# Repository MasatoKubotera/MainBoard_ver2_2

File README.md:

<html lang="en">
  <head>
    <meta charset="uft-8">
    <meta name="author" content="Masato Kubotera">
  </head>
  <body>
    <h1>Main Board Ver. 2.2</h1>
    <h2>About Main Board</h2>
    <p>
      The Main Board is a single board that integrates the circuits for driving the robot designed to be mounted on SUSTAINA-OP.
      <br>
      <br>
      Note that this is Ver. 2.2. For other versions, please refer to the following repositories.
      <ul>
        <li><a href="https://github.com/MasatoKubotera/MainBoard_ver2_0">Main Board Ver. 2.0</a></li>
        <li><a href="https://github.com/MasatoKubotera/MainBoard_ver2_1">Main Board Ver. 2.1</a></li>
      </ul>
      <h2>About Ver. 2.2</h2>
      now writing...
      <br><br>
      It is actually used for the 6th generation robot SUSTAINA-OP of the RoboCup Humanoid League team CIT Brains competed in the RoboCup 2022.<br><br>
      <!--
      -->
      <table>
        <tr>
          <td>
            <a href="image/brd_top.png">
              <div align="center">
                
              </div>
            </a>
          </td>
          <td>
            <div align="center">
              
            </div>
          </td>
          <td>
            <div align="center">
              
            </div>
          </td>
        </tr>
        <tr>
          <td>
            <div align="center">
              PCB preview image
            </div>
          </td>
          <td>
            <div align="center">
              After mounting electronic components
            </div>
          </td>
          <td>
            <div align="center">
              After attaching module board
            </div>
          </td>     
        </tr>
      </table>
    </p>
    <h2>Repository Contents</h2>
    <p>
    <dl>
      <dt>\image</dt>
      <dd>PCB preview images and capture of design screen</dd>
      <dt>\libraries</dt>
      <dd>Libraries used in Autodesk Eagle design</dd>
      <dt>Schematic.pdf</dt>
      <dd>Circuit diagram of this product</dd>
      <dt>BOM.txt</dt>
      <dd>Parts lists output from design data</dd>
      <dt>.brd</dt>
      <dd>Board wiring design file by Autodesk Eagle</dd>
      <dt>.sch</dt>
      <dd>Schematic design file by Autodesk Eagle</dd>
      <dt>Gerber_data.zip</dt>
      <dd>Zip folder of Gerber format files for PCB manufacturing requests.</dd>
      <dt>LICENSE</dt>
      <dd>This is a license to use this product. Please confirm before use.</dd>
      <dt>.gitignore</dt>
      <dd>File to exclude cache files from management.</dd>
    </dl>
    </p>
    <h2>Documentation</h2>
      <p>
        <h3>BOM</h3>
        The BOM below shows the components actually mounted on the SUSTAINA-OP equipped MainBoard in RoboCup2022. Many of these boards have been created, and in some cases substitutes have been used. Their details are listed below the BOM.
          <table>
            <thead>
              <tr>
                <th> Eagle Design Parts # </th>
                <th> Q'ty </th>
                <th> Mfr. Product # </th>
                <th> Supplier </th>
                <th> Description </th>
              </tr>
            </thead>
            <tbody>
              <tr>
                <td>C1, C2, C3, C4, C5, C6</td>
                <td>6</td>
                <td>C1608JB1H104K</td>
                <td><a href="https://akizukidenshi.com/catalog/g/gP-06166/">Akizuki</a></td>
                <td>Multilayer Ceramic Capacitors SMD/SMT 0.1uF 50V 10% 0603</td>
              </tr>
              <tr>
                <td>C11,C15</td>
                <td>2</td>
                <td>UWT1E221MNL1GS</td>
                <td><a href="https://akizukidenshi.com/catalog/g/gP-10420/">Akizuki</a></td>
                <td>Aluminum Electrolytic Capacitors SMD/SMT 220uF 25V 20% AEC-Q200</td>
              </tr>
              <tr>
                <td>C12,C14</td>
                <td>2</td>
                <td>GRM188R71E105KA12</td>
                <td><a href="https://akizukidenshi.com/catalog/g/gP-14526/">Akizuki</a></td>
                <td>Multilayer Ceramic Capacitors SMD/SMT 1uF 25V 10% 0603</td>
              </tr>
              <tr>
                <td>C13</td>
                <td>1</td>
                <td>GRM21BR61E226ME44</td>
                <td><a href="https://akizukidenshi.com/catalog/g/gP-08240/">Akizuki</a></td>
                <td>Multilayer Ceramic Capacitors SMD/SMT 22uF 25V 15% 0603</td>
              </tr>
              <tr>
                <td>C16</td>
                <td>1</td>
                <td>GRM188R6YA106MA73</td>
                <td><a href="https://akizukidenshi.com/catalog/g/gP-13161/">Akizuki</a></td>
                <td>Multilayer Ceramic Capacitors SMD/SMT 10uF 35V 20% 0603</td>
              </tr>
              <tr>
                <td>C7, C8, C9, C10</td>
                <td>4</td>
                <td>35PFV150M8X10.5</td>
                <td><a href="https://akizukidenshi.com/catalog/g/gP-14492/">Akizuki</a></td>
                <td>Aluminum Organic Polymer Capacitors SMD/SMT 150uF 35V 20% AEC-Q200</td>
              </tr>
              <tr>
                <td>CH1, CH2</td>
                <td>2</td>
                <td>XT60PW-M</td>
                <td><a href="https://store.shopping.yahoo.co.jp/suzakulab/amass-xt60pw-m.html">Suzaku Lab.</a></td>
                <td>DC Power Connector, Through Hole, Horizontal, Male, 30A 500V</td>
              </tr>
              <tr>
                <td>CH3</td>
                <td>1</td>
                <td>B2B-XH-A-BLACK</td>
                <td><a href="https://www.daisen-netstore.com/shopdetail/000000000029/ct15/page1/order/">DAISEN</a></td>
                <td>Connector Header Through Hole, Top entry 2 position 2.54mm BLACK</td>
              </tr>
              <tr>
                <td>CH4</td>
                <td>1</td>
                <td>B2B-XH-A-BLUE</td>
                <td><a href="https://www.daisen-netstore.com/shopdetail/000000000029/ct15/page1/order/">DAISEN</a></td>
                <td>Connector Header Through Hole, Top entry 2 position 2.54mm BLUE</td>
              </tr>
              <tr>
                <td>CH5</td>
                <td>1</td>
                <td>B2B-XH-A-GREEN</td>
                <td><a href="https://www.daisen-netstore.com/shopdetail/000000000029/ct15/page1/order/">DAISEN</a></td>
                <td>Connector Header Through Hole, Top entry 2 position 2.54mm GREEN</td>
              </tr>
              <tr>
                <td>CH6</td>
                <td>1</td>
                <td>B2B-XH-A-YELLOW</td>
                <td><a href="https://www.daisen-netstore.com/shopdetail/000000000029/ct15/page1/order/">DAISEN</a></td>
                <td>Connector Header Through Hole, Top entry 2 position 2.54mm YELLOW</td>
              </tr>
              <tr>
                <td>CH7</td>
                <td>1</td>
                <td>B2B-XH-A-RED</td>
                <td><a href="https://www.daisen-netstore.com/shopdetail/000000000029/ct15/page1/order/">DAISEN</a></td>
                <td>Connector Header Through Hole, Top entry 2 position 2.54mm RED</td>
              </tr>
              <tr>
                <td>CH8, CH9</td>
                <td>2</td>
                <td>S4B-XH-A(LF)(SN)-YELLOW</td>
                <td><a href="https://www.daisen-netstore.com/shopdetail/000000000028/ct15/page1/order/">DAISEN</a></td>
                <td>Connector Header Through Hole, Side entry 4 position 2.54mm YELLOW</td>
              </tr>
              <tr>
                <td>CH10</td>
                <td>1</td>
                <td>S4B-XH-A(LF)(SN)-GREEN</td>
                <td><a href="https://www.daisen-netstore.com/shopdetail/000000000028/ct15/page1/order/">DAISEN</a></td>
                <td>Connector Header Through Hole, Side entry 4 position 2.54mm GREEN</td>
              </tr>
              <tr>
                <td>CH11, CH12</td>
                <td>2</td>
                <td>S4B-XH-A(LF)(SN)-BLUE</td>
                <td><a href="https://www.daisen-netstore.com/shopdetail/000000000028/ct15/page1/order/">DAISEN</a></td>
                <td>Connector Header Through Hole, Side entry 4 position 2.54mm BLUE</td>
              </tr>
              <tr>
                <td>CH13</td>
                <td>1</td>
                <td>S4B-XH-A(LF)(SN)-RED</td>
                <td><a href="https://www.daisen-netstore.com/shopdetail/000000000028/ct15/page1/order/">DAISEN</a></td>
                <td>Connector Header Through Hole, Side entry 4 position 2.54mm RED</td>
              </tr>
              <tr>
                <td>D1</td>
                <td>1</td>
                <td>SS34FA</td>
                <td><a href="https://www.mouser.jp/ProductDetail/512-SS34FA">Mouser</a></a></td>
                <td>Schottky Barrier Rectifiers SMD/SMT 3 A 40 V</td>
              </tr>
              <tr>
                <td>F1, F2, F4</td>
                <td>3</td>
                <td>0891020.NXS</td>
                <td><a href="https://www.mouser.jp/ProductDetail/576-0891020.NXS">Mouser</a></td>
                <td>Automotive Fuses LP MINI 58V 20A</td>
              </tr>
              <tr>
                <td>F1, F2, F4, F6</td>
                <td>4</td>
                <td>3557-2</td>
                <td><a href="https://www.mouser.jp/ProductDetail/534-3557-2">Mouser</a></td>
                <td>Fuse Holder Through Hole 500V 30A</td>
              </tr>
              <tr>
                <td>F3</td>
                <td>1</td>
                <td>MF-MSMF010</td>
                <td><a href="https://akizukidenshi.com/catalog/g/gP-15428/">Akizuki</a></td>
                <td>PTC Resettable Fuses SMD/SMT 0.1A 60V 1812</td>
              </tr>
              <tr>
                <td>F5</td>
                <td>1</td>
                <td>MF-MSMF050/30X-2</td>
                <td><a href="https://www.mouser.jp/ProductDetail/652-MF-MSMF050/30X-2">Mouser</a></td>
                <td>PTC Resettable Fuses SMD/SMT 0.5A 30V 1812</td>
              </tr>
              <tr>
                <td>F6</td>
                <td>1</td>
                <td>MO-29</td>
                <td><a href="https://www.amazon.co.jp/dp/B0722VT9DQ/">Amazon</a></td>
                <td>Automotive Fuses LP MINI 7.5A</td>
              </tr>
              <tr>
                <td>IC1, IC2, IC3, IC4</td>
                <td>4</td>
                <td>ADM3078EARZ</td>
                <td><a href="https://www.mouser.jp/ProductDetail/584-ADM3078EARZ">Mouser</a></td>
                <td>3.3 V, ±15 kV ESD-Protected, Half- and Full-Duplex, RS-485/RS-422 Transceivers</td>
              </tr>
              <tr>
                <td>IC5</td>
                <td>1</td>
                <td>LTC4412ES6</td>
                <td><a href="https://akizukidenshi.com/catalog/g/gI-07305/">Akizuki</a></td>
                <td>PMIC Low Loss PowerPath Controller</td>
              </tr>
              <tr>
                <td>L1,L2</td>
                <td>2</td>
                <td>CDRH127/LDNP-470MC</td>
                <td><a href="https://akizukidenshi.com/catalog/g/gP-13966/">Akizuki</a></td>
                <td>Power Inductors - SMD 47uH 3.25A</td>
              </tr>
              <tr>
                <td>L3</td>
                <td>1</td>
                <td>DFE201210S-2R2M</td>
                <td><a href="https://akizukidenshi.com/catalog/g/gP-14976/">Akizuki</a></td>
                <td>Power Inductors - SMD 2.2 uH 1.5A</td>
              </tr>
              <tr>
                <td>LED1,LED2,LED3,LED4</td>
                <td>4</td>
                <td>150060VS86000</td>
                <td><a href="https://www.mouser.jp/ProductDetail/710-150060VS86000">Mouser</a></td>
                <td>Standard LEDs - SMD Green 2V 20mA 573nm 0603</td>
              </tr>
              <tr>
                <td>LED5,LED6</td>
                <td>2</td>
                <td>150060YS75000</td>
                <td><a href="https://www.mouser.jp/ProductDetail/710-150060YS75000">Mouser</a></td>
                <td>Standard LEDs - SMD Yellow 2V 20mA 590nm 0603</td>
              </tr>
              <tr>
                <td>M1</td>
                <td>1</td>
                <td>FT4232H MINI MODULE</td>
                <td><a href="https://www.mouser.jp/ProductDetail/895-FT4232HMINIMOD">Mouser</a></td>
                <td>Interface Development Tools USB Hi-Speed FT4323H Evaluation Module</td>
              </tr>
              <tr>
                <td>M1</td>
                <td>2</td>
                <td>FH-2x13SG</td>
                <td><a href="https://akizukidenshi.com/catalog/g/gC-00084/">Akizuki</a></td>
                <td>2.54mm Pin Socket, 2 Row, 26 Pin</td>
              </tr>
              <tr>
                <td>Q1, Q2, Q3, Q4, Q5</td>
                <td>5</td>
                <td>SQM40P10-40L_GE3</td>
                <td><a href="https://www.mouser.jp/ProductDetail/78-SQM40P10-40L_GE3">Mouser</a></td>
                <td>Pch MOSFET 100V 40A 150W 33mohm</td>
              </tr>
              <tr>
                <td>R1, R3, R4, R6, R7, R9, R10, R12</td>
                <td>8</td>
                <td>RC0603FR-10680RL</td>
                <td><a href="https://www.mouser.jp/ProductDetail/603-RC0603FR-10680RL">Mouser</a></td>
                <td>Thick Film Resistors - SMD 680 Ohms 100-200mW 1% 0603</td>
              </tr>
              <tr>
                <td>R13, R14, R22</td>
                <td>3</td>
                <td>RC0603FR-101KL</td>
                <td><a href="https://www.mouser.jp/ProductDetail/603-RC0603FR-101KL">Mouser</a></td>
                <td>Thick Film Resistors - SMD 1 kOhms 100-200mW 1% 0603</td>
              </tr>
              <tr>
                <td>R15, R16, R20, R23</td>
                <td>4</td>
                <td>RC0603FR-102KL</td>
                <td><a href="https://www.mouser.jp/ProductDetail/603-RC0603FR-102KL">Mouser</a></td>
                <td>Thick Film Resistors - SMD 2 kOhms 100-200mW 1% 0603</td>
              </tr>
              <tr>
                <td>R17</td>
                <td>1</td>
                <td>RC0603FR-10470KL</td>
                <td><a href="https://www.mouser.jp/ProductDetail/603-RC0603FR-10470KL">Mouser</a></td>
                <td>Thick Film Resistors - SMD 470 kOhms 100-200mW 1% 0603</td>
              </tr>
              <tr>
                <td>R21</td>
                <td>1</td>
                <td>RC0603FR-078K66L</td>
                <td><a href="https://www.mouser.jp/ProductDetail/603-RC0603FR-078K66L">Mouser</a></td>
                <td>Thick Film Resistors - SMD 8.66 kOhms 100-200mW 1% 0603</td>
              </tr>
              <tr>
                <td>R18, R19</td>
                <td>2</td>
                <td>RC0603FR-1010KL</td>
                <td><a href="https://www.mouser.jp/ProductDetail/603-RC0603FR-1010KL">Mouser</a></td>
                <td>Thick Film Resistors - SMD 10 kOhms 100-200mW 1% 0603</td>
              </tr>
              <tr>
                <td>R2, R5, R8, R11</td>
                <td>4</td>
                <td>RC0603FR-10120RL</td>
                <td><a href="https://www.mouser.jp/ProductDetail/603-RC0603FR-10120RL">Mouser</a></td>
                <td>Thick Film Resistors - SMD 120 Ohms 100-200mW 1% 0603</td>
              </tr>
              <tr>
                <td>VR1</td>
                <td>1</td>
                <td>XL6009E1</td>
                <td><a href="https://www.aitendo.com/product/10307">Aitendo</a></td>
                <td>400KHz 60V 4A Switching Current Boost / Buck-Boost / Inverting DC/DC Converter</td>
              </tr>
            </tbody>
          </table>
          <details>
            <summary>Substitutes</summary>
            Used for No. 1 ~ No. 7
            <table>
              <thead>
                <tr>
                  <th> Eagle Design Parts # </th>
                  <th> Q'ty </th>
                  <th> Mfr. Product # </th>
                  <th> Supplier </th>
                  <th> Description </th>
                </tr>
              </thead>
              <tbody>
                <tr>
                  <td>C1, C2, C3, C4, C5, C6</td>
                  <td>6</td>
                  <td>GCM188L81H104K57</td>
                  <td><a href="https://akizukidenshi.com/catalog/g/gP-16143/">Akizuki</a></td>
                  <td>Multilayer Ceramic Capacitors SMD/SMT 0.1uF 50V 10% 0603</td>
                </tr>
              </tbody>
            </table>
            Used for No. 13 ~ 
            <table>
              <thead>
                <tr>
                  <th> Eagle Design Parts # </th>
                  <th> Q'ty </th>
                  <th> Mfr. Product # </th>
                  <th> Supplier </th>
                  <th> Description </th>
                </tr>
              </thead>
              <tbody>
                <tr>
                  <td>Q1, Q2, Q3, Q4, Q5</td>
                  <td>5</td>
                  <td>SUM110P06-08L-E3</td>
                  <td><a href="https://www.mouser.jp/ProductDetail/781-SUM110P06-08L-E3">Mouser</a></td>
                  <td>Pch MOSFET 60V 110A 272W 8.0mohm</td>
                </tr>
              </tbody>
            </table>
          </details>  
        <h3>PCB Fabrication</h3>
          PCB(Printed Circuit Board) manufacturing was outsourced to <a href="https://www.elecrow.com/pcb-manufacturing.html">Elecrow</a>.<br>
          The custom specifications are as follows.
          <ul>
            <li>Layer : 2 layers</li>
            <li>Dimensions : 120 x 65</li>
            <li>Different PCB Design : 1eg</li>
            <li>PCB Thickness : 1.6</li>
            <li>PCB Color : Black</li>
            <li>Surface Finish : HASL Lead Free</li>
            <li>Castellated Hole : No</li>
            <li>Copper Weight : 2oz</li>
            <li>PCB Stencil : Stencil 15cm X 15cm no frame</li>
            <li>Stencil Side : Top</li>
          </ul>
          The data used to order fabrication are as follows.
          <ul>
            <li>Eagle design rule : <a href="https://www.elecrow.com/download/Elecrow_PCB_eagle_rule.zip">Elecrow Eagle Design Rule</a></li>
            <li>Eagle CAM file : <a href="https://www.elecrow.com/download/Elecrow_Gerber_Generater_DrillAlign.zip">Elecrow CAM file</a></li>
            <li>Gerber format data : <a href="/Gerber_data.zip">Gerber_data.zip</a></li>
          </ul>
        <h3>Issues with this board</h3>
        <ul>
          <li>Heat generation problem of FETs</li>
          <li>Poor inrush current protection by load switch circuit</li>
        </ul>
        <h3>References</h3>
        <ul>
          <li> 4-Parallel Servo Motor Control with FT4232H MINI MODULE
            <ul>
              <li> <a href=""https://2019.robocup.org/downloads/program/BestmannEtAl2019.pdf">Bestmann, Marc & Güldenstein, Jasper & Zhang, Jianwei. (2019). High-Frequency Multi Bus Servo and Sensor Communication Using the Dynamixel Protocol. </a></li>
              <li> Wolfgang CORE : https://github.com/bit-bots/wolfgang_core</li>
             </ul>
          </li>
        </ul>
      </p>
    <h2>Contact</h2>
    <p>
    If you have any questions, please contact MasatoKubotera, the product's designer, by E-mail.<br>
    E-mail : <a href="mailto:masatokubotera06@yahoo.co.jp">masatokubotera06@yahoo.co.jp</a>
    </p>
    <h2>License Information</h2>
    <p>
      This product is open source.<br>
      Please review the <a href="/LICENSE">LICENSE file</a> for license information.<br>
      <br>
      <strong>Main Board Ver. 2.2</strong> by Masato Kubotera is licensed under a <a href="http://creativecommons.org/licenses/by-nc-sa/4.0/">Creative Commons Attribution-NonCommercial-ShareAlike 4.0 International License</a>.
    </p>    
  </body>
</html>

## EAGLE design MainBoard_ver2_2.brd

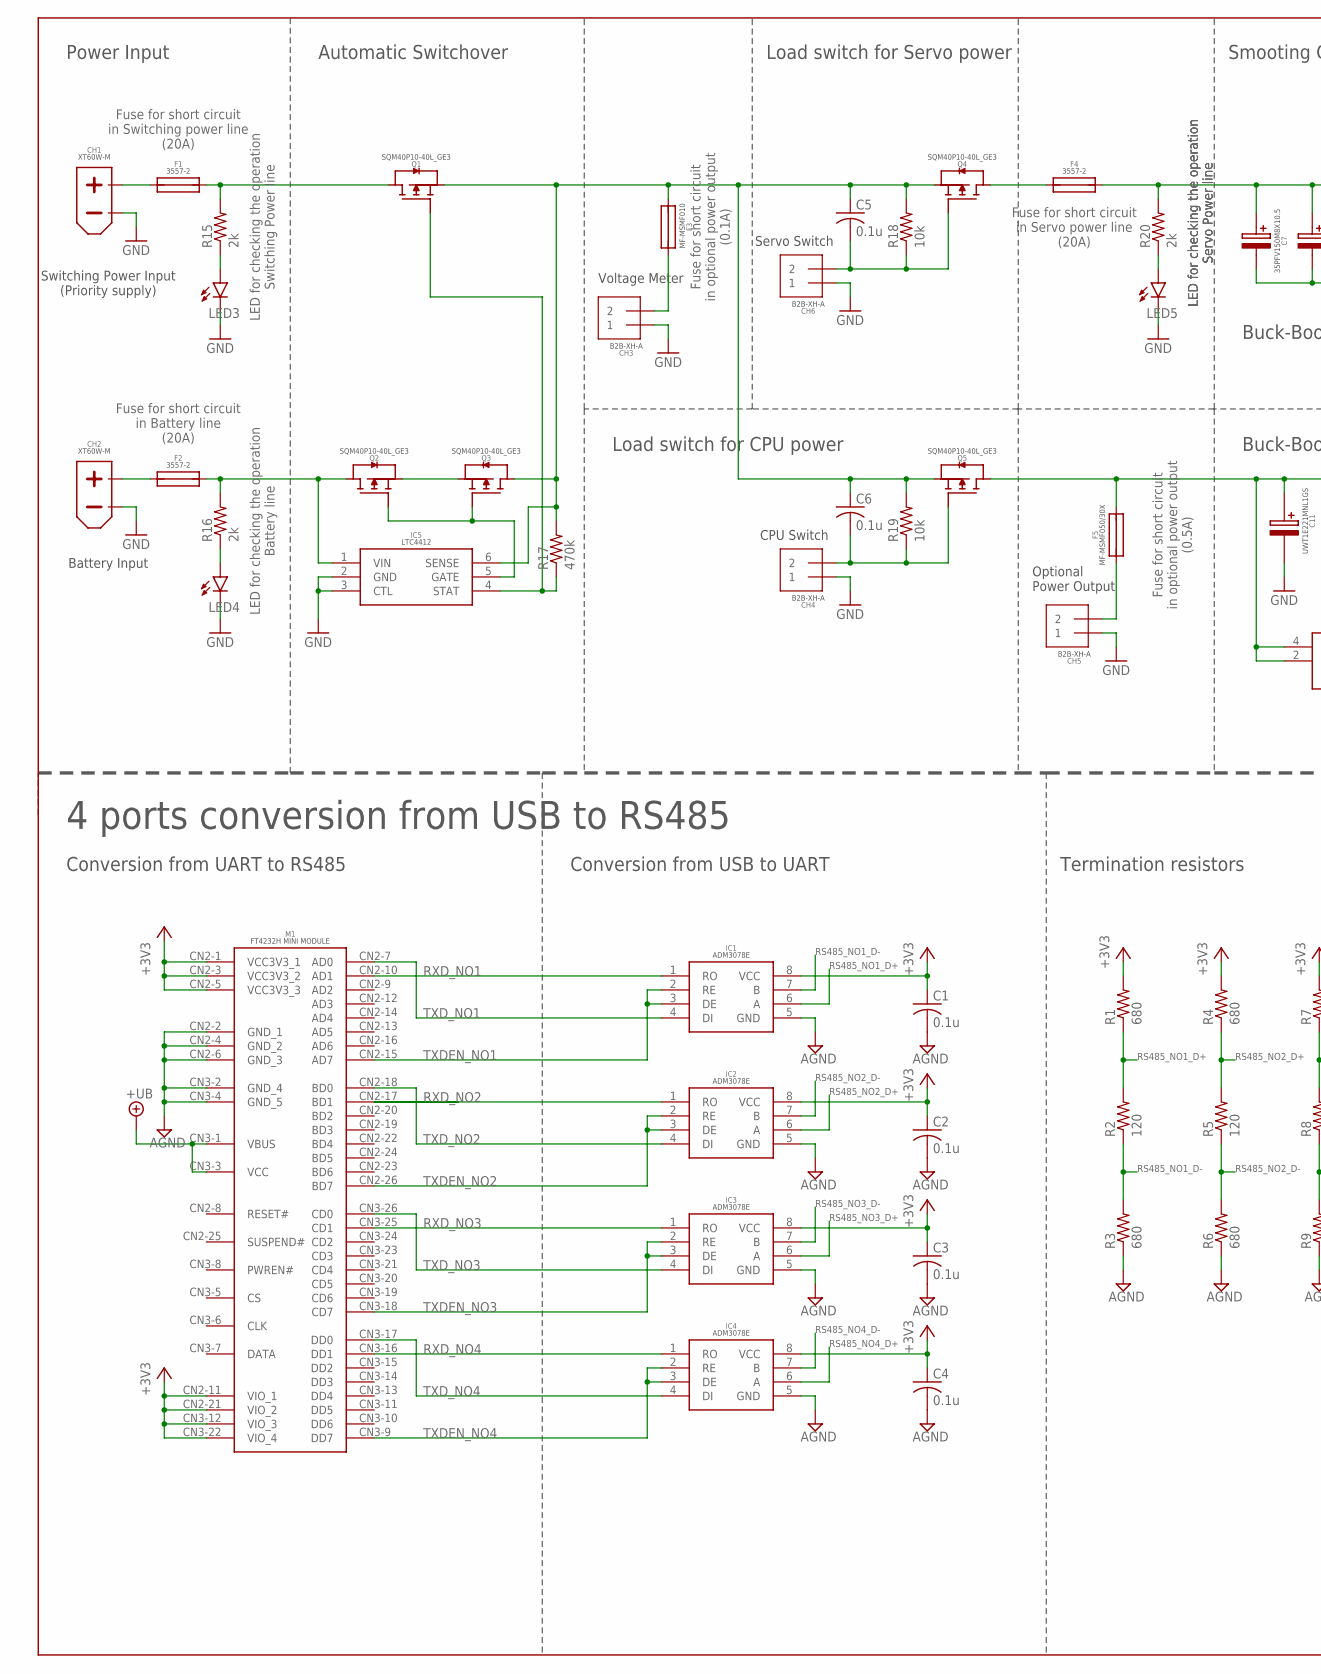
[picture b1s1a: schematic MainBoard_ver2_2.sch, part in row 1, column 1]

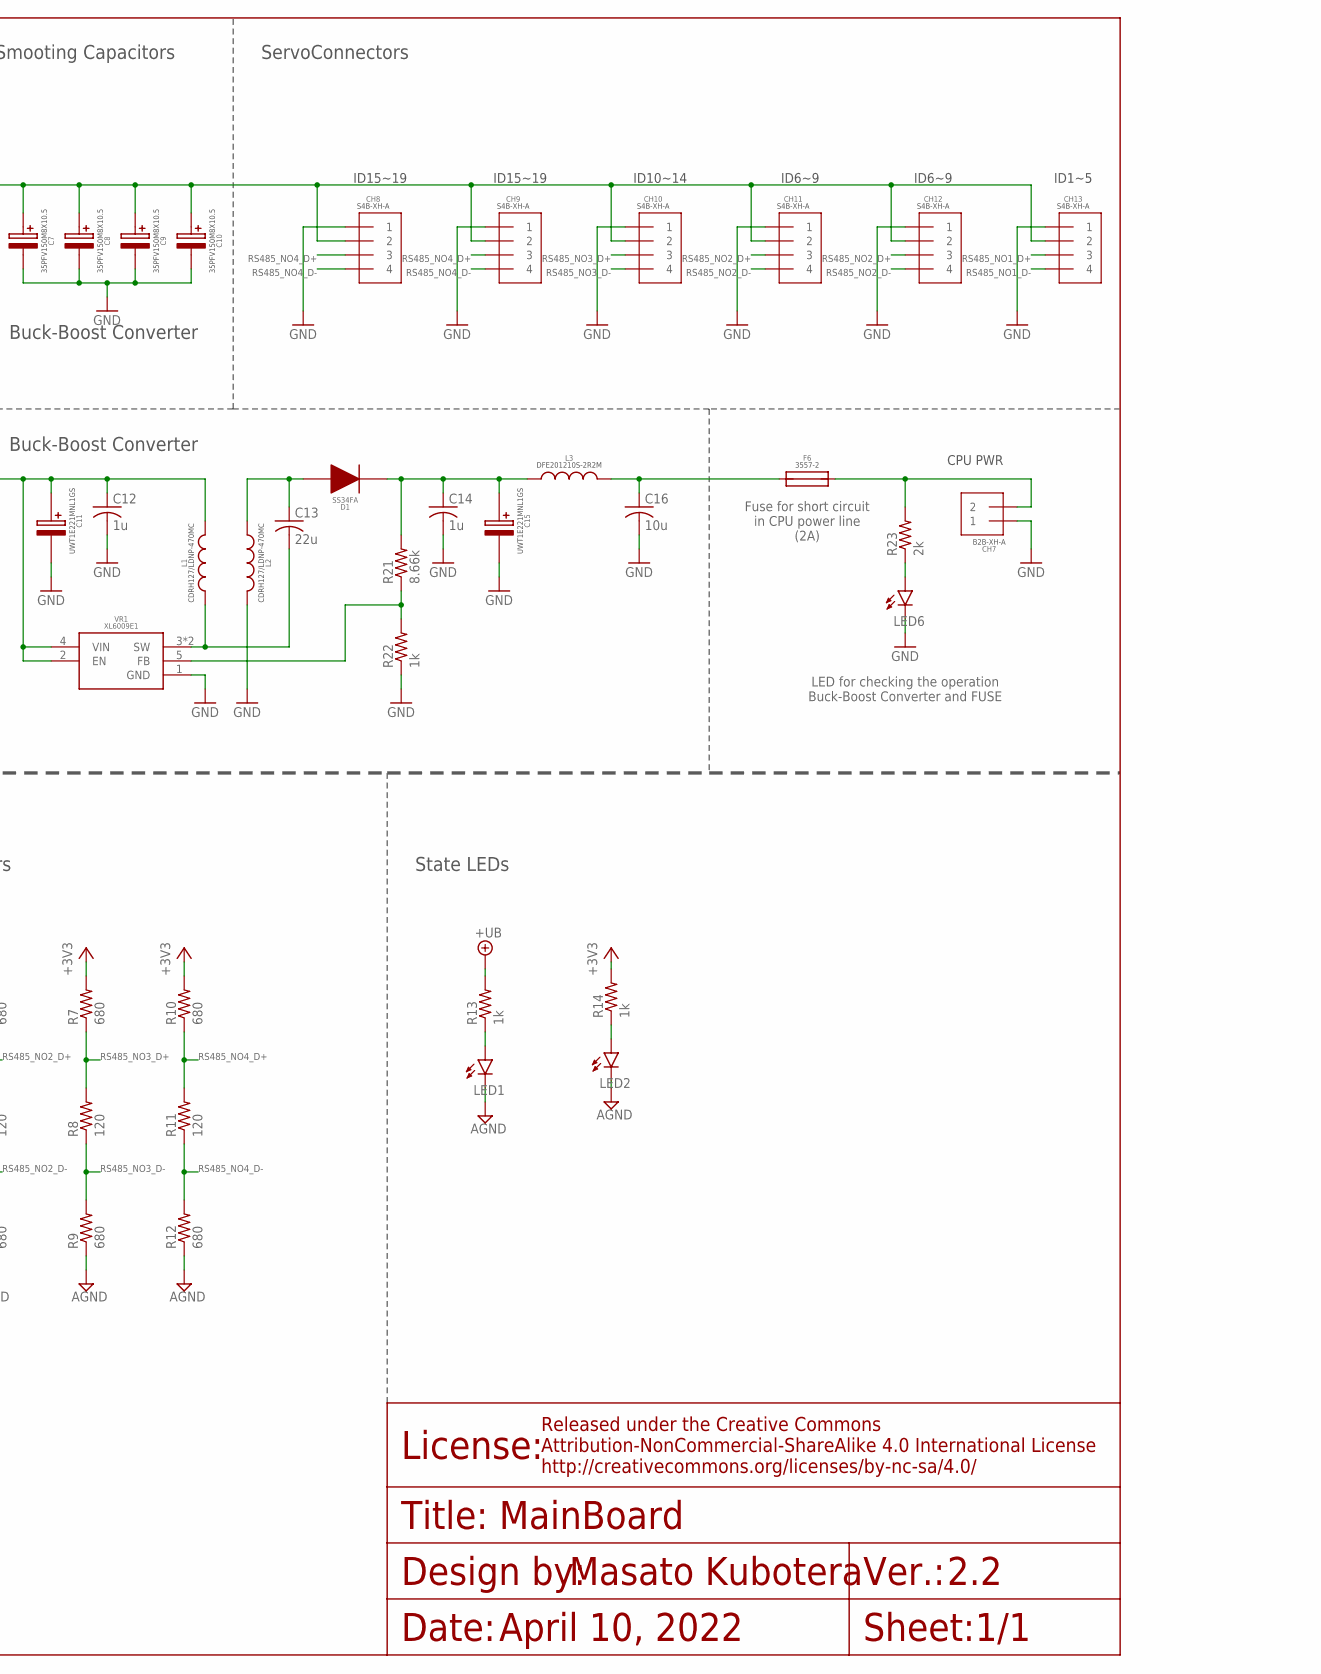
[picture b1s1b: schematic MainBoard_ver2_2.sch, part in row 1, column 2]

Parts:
C1, C2, C3, C4, C5, C6: 0.1u; C0603
C7, C8, C9, C10: 35PFV150M8X10.5
C11, C15: UWT1E221MNL1GS
C12, C14: 1u; C0603
C13: 22u; C2012
C16: 10u; C0603
CH1, CH2: XT60PW-M
CH3, CH4, CH5, CH6, CH7: B2B-XH-A
CH8, CH9, CH10, CH11, CH12, CH13: S4B-XH-A
D1: SS34FA
F1, F2, F4, F6: 3557-2
F3: MF-MSMF010
F5: MF-MSMF050/30X; MF-MSMF050
IC1, IC2, IC3, IC4: ADM3078E
IC5: LTC4412
L1, L2: CDRH127/LDNP-470MC; CDRH127/LDNP
L3: DFE201210S-2R2M; DFE201210S
LED1, LED2, LED3, LED4, LED5, LED6: LEDSML0603; SML0603
M1: FT4232H_MINI_MODULE
Q1, Q2, Q3, Q4, Q5: SQM40P10-40L_GE3; TO-252-3
R1, R3, R4, R6, R7, R9, R10, R12: 680; R0603
R2, R5, R8, R11: 120; R0603
R13, R14, R22: 1k; R0603
R15, R16, R20, R23: 2k; R0603
R17: 470k; R0603
R18, R19: 10k; R0603
R21: 8.66k; R0603
VR1: XL6009E1; TO263-5L

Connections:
+3V3: C1.1, C2.1, C3.1, C4.1, IC1.8 (VCC), IC2.8 (VCC), IC3.8 (VCC), IC4.8 (VCC), M1.CN2-1 (VCC3V3_1), M1.CN2-3 (VCC3V3_2), M1.CN2-5 (VCC3V3_3), M1.CN2-11 (VIO_1), M1.CN2-21 (VIO_2), M1.CN3-12 (VIO_3), M1.CN3-22 (VIO_4), R1.2, R4.2, R7.2, R10.2, R14.2
+UB: M1.CN3-1 (VBUS), M1.CN3-3 (VCC), R13.2
AGND: C1.2, C2.2, C3.2, C4.2, IC1.5 (GND), IC2.5 (GND), IC3.5 (GND), IC4.5 (GND), LED1.C, LED2.C, M1.CN2-2 (GND_1), M1.CN2-4 (GND_2), M1.CN2-6 (GND_3), M1.CN3-2 (GND_4), M1.CN3-4 (GND_5), R3.1, R6.1, R9.1, R12.1
A_DIODE_DCDC: C14.1, C15.+, D1.1, L3.1, R21.2
A_FUSE_BATT: F2.3 (2), F2.4 (2), IC5.1 (VIN), Q2.4 (D), R16.2
A_FUSE_DCDC: CH7.2, F6.3 (2), F6.4 (2), R23.2
A_FUSE_METER: CH3.2, F3.2
A_FUSE_PWR: F1.3 (2), F1.4 (2), Q1.4 (D), R15.2
A_FUSE_SERVO: C7.+, C8.+, C9.+, C10.+, CH8.2, CH9.2, CH10.2, CH11.2, CH12.2, CH13.2, F4.3 (2), F4.4 (2), R20.2
B_DIODE_DCDC: C13.1, D1.2, L2.1
B_FUSE_BATT: CH2.+, F2.1, F2.2 (1)
B_FUSE_DCDC: C16.1, F6.1, F6.2 (1), L3.2
B_FUSE_PWR: CH1.+, F1.1, F1.2 (1)
B_FUSE_SERVO: F4.1, F4.2 (1), Q4.4 (D)
B_LOAD_CPU: C6.2, CH4.2, Q5.1 (G), R19.1
B_LOAD_SERVO: C5.2, CH6.2, Q4.1 (G), R18.1
CPU_PWR_IN: C11.+, C12.1, F5.2, L1.2, Q5.4 (D), VR1.2 (EN), VR1.4 (VIN)
FB_DCDC: R21.1, R22.2, VR1.5 (FB)
GND: C7.-, C8.-, C9.-, C10.-, C11.-, C12.2, C14.2, C15.-, C16.2, CH1.-, CH2.-, CH3.1, CH4.1, CH5.1, CH6.1, CH7.1, CH8.1, CH9.1, CH10.1, CH11.1, CH12.1, CH13.1, IC5.2 (GND), IC5.3 (CTL), L2.2, LED3.C, LED4.C, LED5.C, LED6.C, R22.1, VR1.1 (GND)
INPUT_PWR: C5.1, C6.1, F3.1, IC5.6 (SENSE), Q1.3 (S), Q3.4 (D), Q4.3 (S), Q5.3 (S), R17.2, R18.2, R19.2
LED_3V3: LED2.A, R14.1
LED_BATT: LED4.A, R16.1
LED_DCDCOUT: LED6.A, R23.1
LED_PWR: LED3.A, R15.1
LED_SERVO: LED5.A, R20.1
LED_UB: LED1.A, R13.1
LTC4412_GATE: IC5.5 (GATE), Q2.1 (G), Q3.1 (G)
LTC4412_STAT: IC5.4 (STAT), Q1.1 (G), R17.1
POWER_OUTPUT: CH5.2, F5.1
RS485_NO1_D+: CH13.3, IC1.6 (A), R1.1, R2.2
RS485_NO1_D-: CH13.4, IC1.7 (B), R2.1, R3.2
RS485_NO2_D+: CH11.3, CH12.3, IC2.6 (A), R4.1, R5.2
RS485_NO2_D-: CH11.4, CH12.4, IC2.7 (B), R5.1, R6.2
RS485_NO3_D+: CH10.3, IC3.6 (A), R7.1, R8.2
RS485_NO3_D-: CH10.4, IC3.7 (B), R8.1, R9.2
RS485_NO4_D+: CH8.3, CH9.3, IC4.6 (A), R10.1, R11.2
RS485_NO4_D-: CH8.4, CH9.4, IC4.7 (B), R11.1, R12.2
RXD_NO1: IC1.1 (RO), M1.CN2-10 (AD1)
RXD_NO2: IC2.1 (RO), M1.CN2-17 (BD1)
RXD_NO3: IC3.1 (RO), M1.CN3-25 (CD1)
RXD_NO4: IC4.1 (RO), M1.CN3-16 (DD1)
SOURCE: Q2.3 (S), Q3.3 (S)
SW_DCDC: C13.2, L1.1, VR1.3 (SW), VR1.6 (SW)
TXDEN_NO1: IC1.2 (RE), IC1.3 (DE), M1.CN2-15 (AD7)
TXDEN_NO2: IC2.2 (RE), IC2.3 (DE), M1.CN2-26 (BD7)
TXDEN_NO3: IC3.2 (RE), IC3.3 (DE), M1.CN3-18 (CD7)
TXDEN_NO4: IC4.2 (RE), IC4.3 (DE), M1.CN3-9 (DD7)
TXD_NO1: IC1.4 (DI), M1.CN2-7 (AD0)
TXD_NO2: IC2.4 (DI), M1.CN2-18 (BD0)
TXD_NO3: IC3.4 (DI), M1.CN3-26 (CD0)
TXD_NO4: IC4.4 (DI), M1.CN3-17 (DD0)

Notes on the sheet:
CPU Switch
Battery Input
Switching Power Input (Priority supply)
Servo Switch
Voltage Meter
Optional Power Output
ServoConnectors
Buck-Boost Converter
Smooting Capacitors
LED for checking the operation Buck-Boost Converter and FUSE
Fuse for short circuit in CPU power line (2A)
CPU PWR
Fuse for short circuit in Servo power line (20A)
Load switch for Servo power
Load switch for CPU power
Fuse for short circuit in optional power output (0.5A)
Automatic Switchover
Fuse for short circuit in Switching power line (20A)
Fuse for short circuit in Battery line (20A)
LED for checking the operation Switching Power line
LED for checking the operation Battery line
Fuse for short circuit in optional power output (0.1A)
LED for checking the operation Servo Power line
ID1~5
ID6~9
ID10~14
ID15~19
4 ports conversion from USB to RS485
Conversion from USB to UART
Termination resistors
State LEDs
2.2
1/1
April 10, 2022
MainBoard
Conversion from UART to RS485
Power Input

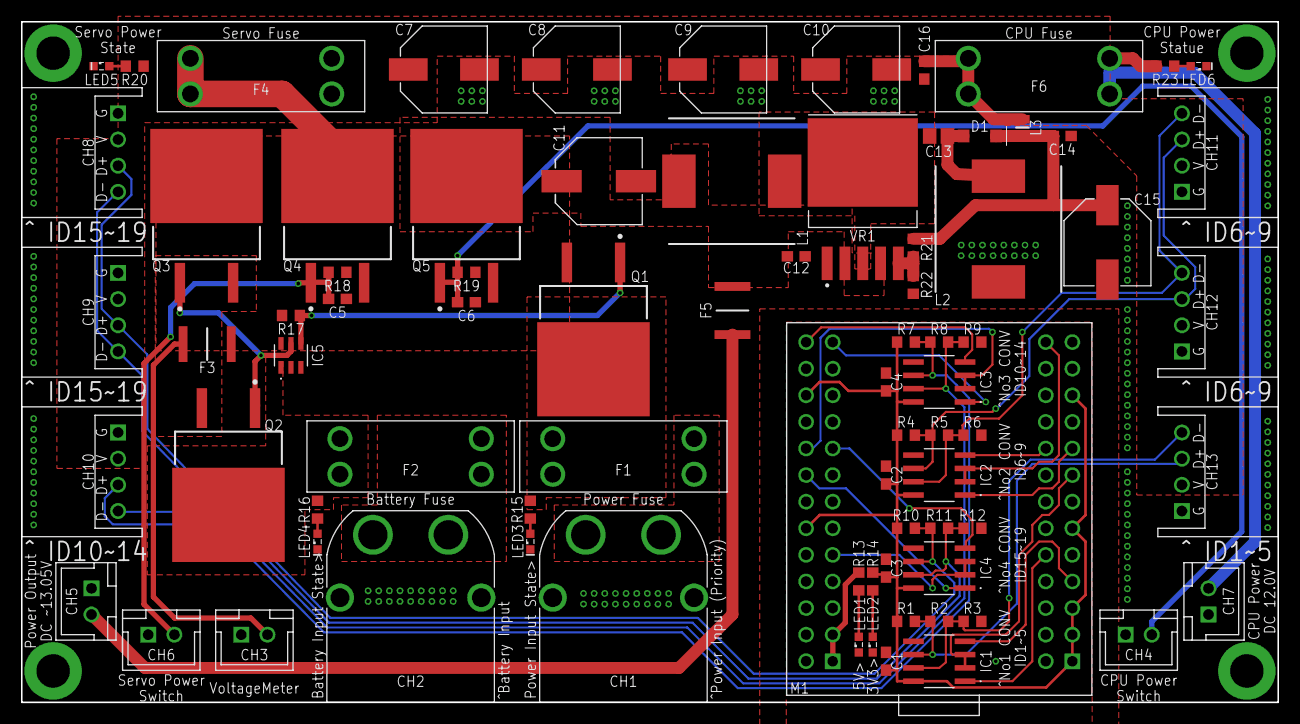
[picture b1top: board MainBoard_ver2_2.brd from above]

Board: 2 copper layers, 120.0 x 65.0 mm, 80 parts (0 on the bottom side), 51 nets.

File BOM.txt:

Partlist exported from C:/Users/Masato/Documents/citbrains/MainBoard_ver2_2/MainBoard_ver2_2.sch at 2022/09/21 4:07

Qty Value               Device              Package             Parts                              Description                
6                       LEDSML0603          SML0603             LED1, LED2, LED3, LED4, LED5, LED6 LED                        
6   0.1u                C-USC0603           C0603               C1, C2, C3, C4, C5, C6             CAPACITOR, American symbol 
2   10k                 R-US_R0603          R0603               R18, R19                           RESISTOR, American symbol  
1   10u                 C-USC0603           C0603               C16                                CAPACITOR, American symbol 
4   120                 R-US_R0603          R0603               R2, R5, R8, R11                    RESISTOR, American symbol  
3   1k                  R-US_R0603          R0603               R13, R14, R22                      RESISTOR, American symbol  
2   1u                  C-USC0603           C0603               C12, C14                           CAPACITOR, American symbol 
1   22u                 C-USC2012           C2012               C13                                CAPACITOR, American symbol 
4   2k                  R-US_R0603          R0603               R15, R16, R20, R23                 RESISTOR, American symbol  
4   3557-2              3557-2              3557-2              F1, F2, F4, F6                                                
4   35PFV150M8X10.5     35PFV150M8X10.5     35PFV150M8X10.5     C7, C8, C9, C10                                               
1   470k                R-US_R0603          R0603               R17                                RESISTOR, American symbol  
8   680                 R-US_R0603          R0603               R1, R3, R4, R6, R7, R9, R10, R12   RESISTOR, American symbol  
1   8.66k               R-US_R0603          R0603               R21                                RESISTOR, American symbol  
4   ADM3078E            ADM3078E            ADM3078E            IC1, IC2, IC3, IC4                                            
5   B2B-XH-A            B2B-XH-A            B2B-XH-A            CH3, CH4, CH5, CH6, CH7                                       
2   CDRH127/LDNP-470MC  CDRH127/LDNP-470MC  CDRH127/LDNP        L1, L2                                                        
1   DFE201210S-2R2M     DFE201210S-2R2M     DFE201210S          L3                                                            
1   FT4232H_MINI_MODULE FT4232H_MINI_MODULE FT4232H_MINI_MODULE M1                                                            
1   LTC4412             LTC4412             LTC4412             IC5                                                           
1   MF-MSMF010          MF-MSMF010          MF-MSMF010          F3                                                            
1   MF-MSMF050/30X      MF-MSMF050/30X      MF-MSMF050          F5                                                            
6   S4B-XH-A            S4B-XH-A            S4B-XH-A            CH8, CH9, CH10, CH11, CH12, CH13                              
5   SQM40P10-40L_GE3    SQM40P10-40L_GE3    TO-252-3            Q1, Q2, Q3, Q4, Q5                                            
1   SS34FA              SS34FA              SS34FA              D1                                                            
2   UWT1E221MNL1GS      UWT1E221MNL1GS      UWT1E221MNL1GS      C11, C15                                                      
1   XL6009E1            XL6009E1            TO263-5L            VR1                                                           
2   XT60PW-M            XT60PW-M            XT60PW-M            CH1, CH2

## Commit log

2022-09-20 Initial upload of data
2022-09-23 Update LICENSE

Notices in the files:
README.md:
Main Board Ver. 2.2 by Masato Kubotera is licensed under a Creative Commons Attribution-NonCommercial-ShareAlike 4.0 International License.
parts and their libraries:
Frame: Released under the Creative Commons
Attribution-NonCommercial-ShareAlike 4.0 International License
http://creativecommons.org/licenses/by-nc-sa/4.0
